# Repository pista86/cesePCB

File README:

El PCB ha sido desarrollado en el marco de la realización del prototipo funcional de proyecto:

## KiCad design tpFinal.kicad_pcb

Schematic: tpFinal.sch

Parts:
C9: 0.1uF; C_0805_2012Metric
C10: 10uF; C_0805_2012Metric
FD1, FD2, FD3: Fiducial; Fiducial_1mm_Dia_2mm_Outer
MH1, MH2, MH3, MH4: MountingHole_Pad; MountingHole_2.2mm_M2_Pad_Via
P1: CONN_UART_TX_RX
P2: CONN_SPK
P3: CONN_PWR
P4: CONN_BAT
P5: CONN_SWD
R9, R10: 10K; R_0805_2012Metric
U1: EMW3166

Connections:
+3V3: C9.2, C10.1, P5.1, U1.10, U1.39, U1.40; also elsewhere on the board
+BATT: P4.1, R9.2; also elsewhere on the board
+VDC: P3.1; also elsewhere on the board
/AMPLIFICADOR_BCLK: U1.6; also elsewhere on the board
/AMPLIFICADOR_DIN: U1.4; also elsewhere on the board
/AMPLIFICADOR_LRCLK: U1.5; also elsewhere on the board
/AMPLIFICADOR_SD_MODE: U1.7; also elsewhere on the board
/CARGADOR_STAT: U1.2; also elsewhere on the board
/LED_B: U1.17; also elsewhere on the board
/LED_G: U1.18; also elsewhere on the board
/LED_R: U1.29; also elsewhere on the board
/LED_Y: U1.12; also elsewhere on the board
/MIC_CLK: U1.37; also elsewhere on the board
/MIC_DATA: U1.33; also elsewhere on the board
/NRST: P5.4, U1.13
/SWCLK: P5.2, U1.25
/SWDIO: P5.3, U1.26
/SW_B: U1.30; also elsewhere on the board
/SW_G: U1.19; also elsewhere on the board
/SW_R: U1.27; also elsewhere on the board
/SW_Y: U1.31; also elsewhere on the board
/UART_Rx: P1.2, U1.36
/UART_Tx: P1.1, U1.35
/amplificadorAudioDigital/OUT+: P2.1; also elsewhere on the board
/amplificadorAudioDigital/OUT-: P2.2; also elsewhere on the board
GND: C9.1, C10.2, MH1.1, MH2.1, MH3.1, MH4.1, P1.3, P3.2, P4.2, P5.5, R10.2, U1.20, U1.21; also elsewhere on the board
unnamed: R9.1, R10.1, U1.38

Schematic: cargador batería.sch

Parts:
C1, C2: 10uF; C_0805_2012Metric
R1: 2K; R_0805_2012Metric
U2: MCP73831-2-OT; SOT-23-5

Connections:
+BATT: C2.1, U2.3 (VBAT); also elsewhere on the board
+VDC: C1.1, U2.4 (VDD); also elsewhere on the board
/CARGADOR_STAT: U2.1 (STAT); also elsewhere on the board
GND: C1.2, C2.2, R1.2, U2.2 (VSS); also elsewhere on the board
unnamed: R1.1, U2.5 (PROG)

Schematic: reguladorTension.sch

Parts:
C3, C5: 10uF; C_0805_2012Metric
C4: 15pF; C_0805_2012Metric
L1: 2.2uH; L_1210_3225Metric
R2: 453K; R_0805_2012Metric
R3: 100k; R_0805_2012Metric
U3: AUR9705AGH; SOT-23-5

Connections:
+3V3: C4.1, C5.1, L1.2, R2.1; also elsewhere on the board
+BATT: C3.1, U3.1, U3.3; also elsewhere on the board
GND: C3.2, C5.2, R3.2, U3.2; also elsewhere on the board
unnamed: C4.2, R2.2, R3.1, U3.4
unnamed: L1.1, U3.5

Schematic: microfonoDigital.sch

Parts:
C6: 0.1uF; C_0805_2012Metric
U4: SPH0644HM4H-1

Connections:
+3V3: C6.2, U4.1; also elsewhere on the board
/MIC_CLK: U4.2; also elsewhere on the board
/MIC_DATA: U4.3; also elsewhere on the board
GND: C6.1, U4.4, U4.5, U4.6; also elsewhere on the board

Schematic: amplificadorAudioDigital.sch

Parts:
C7: 10uF; C_0805_2012Metric
C8: 0.1uF; C_0805_2012Metric
R4: 100K; R_0805_2012Metric
U5: MAX98357A; QFN-16-1EP_3x3mm_P0.5mm_EP1.8x1.8mm

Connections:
+BATT: C7.1, C8.1, R4.2, U5.7, U5.8; also elsewhere on the board
/AMPLIFICADOR_BCLK: U5.16; also elsewhere on the board
/AMPLIFICADOR_DIN: U5.1; also elsewhere on the board
/AMPLIFICADOR_LRCLK: U5.14; also elsewhere on the board
/AMPLIFICADOR_SD_MODE: U5.4; also elsewhere on the board
/amplificadorAudioDigital/GAIN_SLOT: R4.1, U5.2
/amplificadorAudioDigital/OUT+: U5.9; also elsewhere on the board
/amplificadorAudioDigital/OUT-: U5.10; also elsewhere on the board
GND: C7.2, C8.2, U5.3, U5.11, U5.15, U5.17; also elsewhere on the board

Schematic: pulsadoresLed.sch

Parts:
R5: 470R; R_0805_2012Metric
R6: 220R; R_0805_2012Metric
R7: 330R; R_0805_2012Metric
R8: 270R; R_0805_2012Metric
SWB1: TS12I
SWG1: TS12I
SWR1: TS12I
SWY1: TS12I

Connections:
/LED_B: SWB1.5; also elsewhere on the board
/LED_G: SWG1.5; also elsewhere on the board
/LED_R: SWR1.5; also elsewhere on the board
/LED_Y: SWY1.5; also elsewhere on the board
/SW_B: SWB1.1, SWB1.2; also elsewhere on the board
/SW_G: SWG1.1, SWG1.2; also elsewhere on the board
/SW_R: SWR1.1, SWR1.2; also elsewhere on the board
/SW_Y: SWY1.1, SWY1.2; also elsewhere on the board
GND: R5.2, R6.2, R7.2, R8.2, SWB1.3, SWB1.4, SWG1.3, SWG1.4, SWR1.3, SWR1.4, SWY1.3, SWY1.4; also elsewhere on the board
unnamed: R5.1, SWR1.6
unnamed: R6.1, SWB1.6
unnamed: R7.1, SWG1.6
unnamed: R8.1, SWY1.6

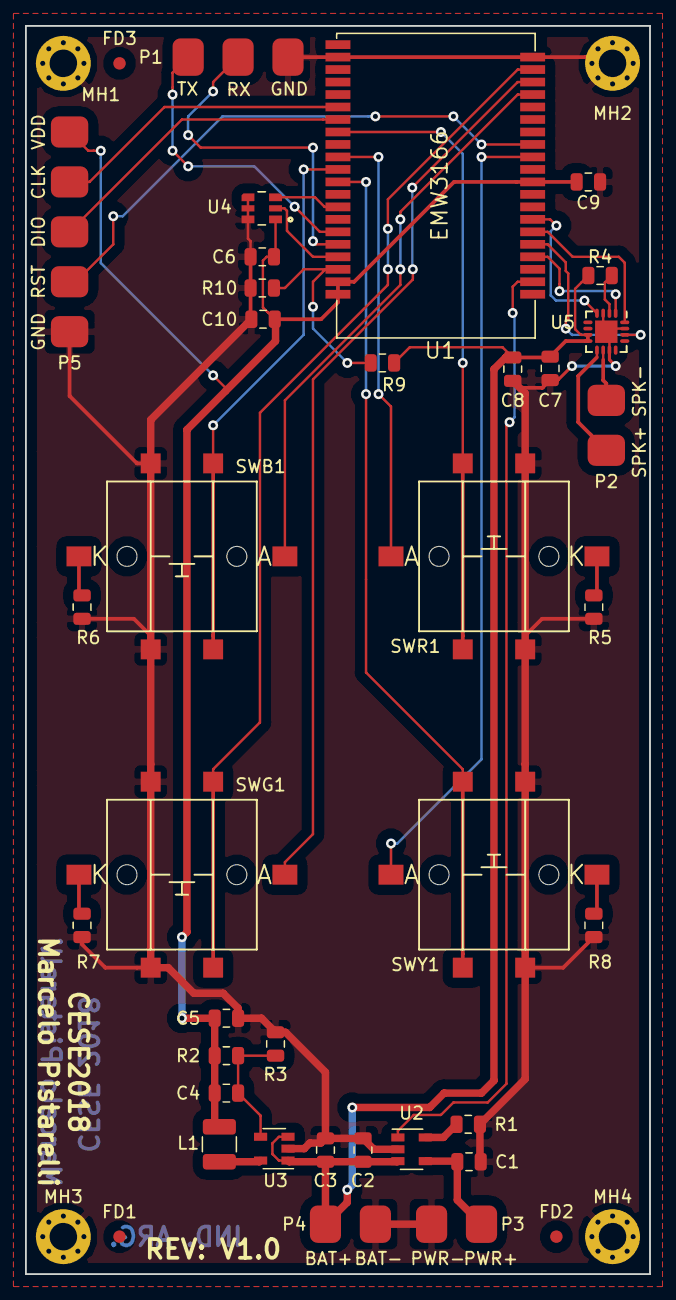
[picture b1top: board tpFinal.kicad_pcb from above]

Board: 2 copper layers, 50.0 x 100.0 mm, 42 parts (0 on the bottom side), 35 nets.

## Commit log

2018-10-16 Esquema
2018-10-19 Esquema corregido, PCB terminada
2018-10-19 correción de paths
2018-10-19 correciones varias según revisiones
2018-11-28 Se aplicaron correciones indicadas por el profesor en el esquemático
2018-11-28 Corrección de licencia, se agrega hoja de datos de tact switch
2018-11-28 Se agregan reglas de fabricación de SeeedStudio, e información sobre el proyecto
2018-11-28 Referencias de fiduciales y agujeros de sujeción configuradas invisibles
2018-11-28 Se colocaron modelos 3D en carpeta shapes3D
